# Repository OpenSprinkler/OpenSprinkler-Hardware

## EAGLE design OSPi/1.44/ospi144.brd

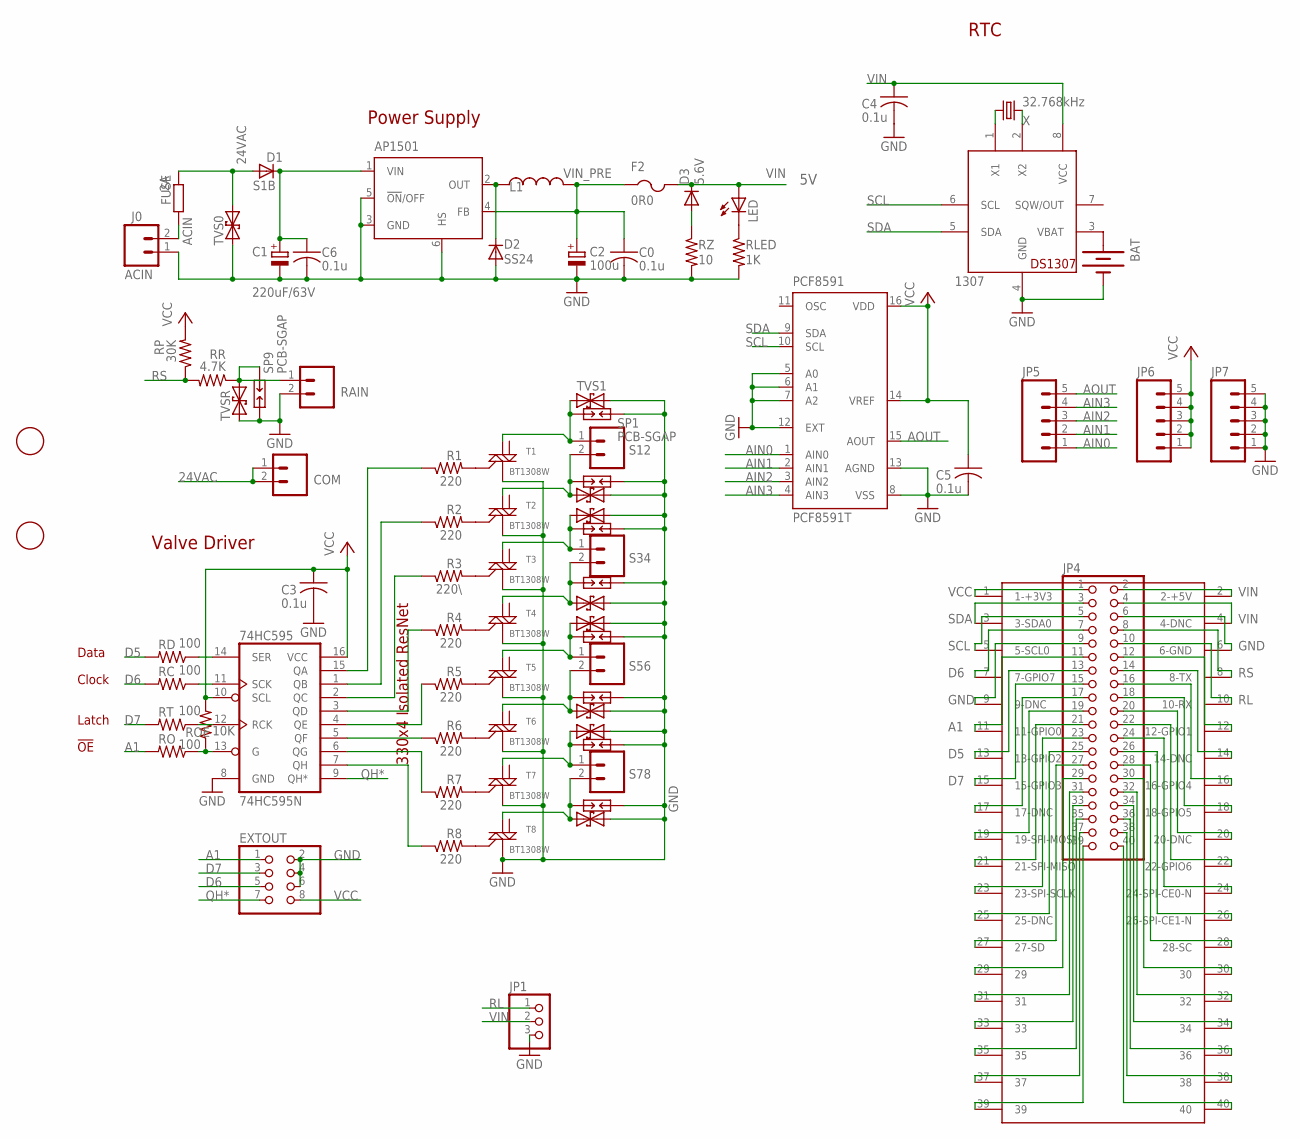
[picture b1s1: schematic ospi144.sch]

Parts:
74HC595: 74HC595N; SO16
1307: DS1307; SO08
AP1501: LM2596S; TO263-5
BAT: BATTERYBATTERY_12MM_SMT; BATTCON_12MM_SMT
C0, C3, C4, C5, C6: 0.1u; C0603K
C1: 220uF/63V; PANASONIC_E
C2: 100u; PANASONIC_E
COM: M025MM-X; SCREWTERMINAL-5MM-2-X
D1: S1B; DO-214AC
D2: SS24; SMB
D3: 5.6V; MINIMELF
EXTOUT: PINHD-2X4/90; 2X04/90
F2: 0R0; 1812
FUSE: 2A; 0207/12
J0: ACIN; SCREWTERMINAL-4MM-2-X
JP1: PINHD-1X3; 1X03
JP4: PINHD-2X20; 2X20
JP5, JP6, JP7: M05PTH; 1X05
L1: 150uH; CDRH125
LED: LEDCHIPLED_0805; CHIPLED_0805
PCF8591: PCF8591T; SO16W
R1, R2, R4, R5, R6, R7, R8: 220; R0603
R3: 220\; R0603
RAIN: M025MM-X; SCREWTERMINAL-5MM-2-X
RC: 100; R0603
RD: 100; R0603
RLED: 1K; R0805
RO: 100; R0603
ROE: 10K; R0603
RP: 30K; R0805
RR: 4.7K; R0805
RT: 100; R0603
RZ: 10; R2010
S12, S34, S56, S78: M025MM-X; SCREWTERMINAL-5MM-2-X
SP1, SP2, SP3, SP4, SP5, SP6, SP7, SP8, SP9: PCB-SGAP
T1, T2, T3, T4, T5, T6, T7, T8: BT1308W; SOT223
TVS0, TVS1, TVS2, TVS3, TVS4, TVS5, TVS6, TVS7, TVS8: TVSSMB; SMB
TVSR: TVSSMB; SMB
U$1, U$3: FIDUCIAL; FIDUCIAL_1MM
U$2: RPIB+
X: 32.768kHz; MM20SS

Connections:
24VAC: COM.1, COM.2, D1.A, FUSE.2, TVS0.C
A1: EXTOUT.1, JP4.11, RO.2, U$2.11 (11-GPIO0)
ACIN: FUSE.1, J0.2
AIN0: JP5.1, PCF8591.1 (AIN0)
AIN1: JP5.2, PCF8591.2 (AIN1)
AIN2: JP5.3, PCF8591.3 (AIN2)
AIN3: JP5.4, PCF8591.4 (AIN3)
AOUT: JP5.5, PCF8591.15 (AOUT)
D5: JP4.13, RD.2, U$2.13 (13-GPIO2)
D6: EXTOUT.5, JP4.7, RC.2, U$2.7 (7-GPIO7)
D7: EXTOUT.3, JP4.15, RT.2, U$2.15 (15-GPIO3)
GND: 74HC595.8 (GND), 1307.4 (GND), AP1501.3 (GND), AP1501.5 (!ON!/OFF), AP1501.6 (HS), BAT.P$1 (-), C0.2, C1.-, C2.-, C3.2, C4.2, C5.2, C6.2, D2.A, EXTOUT.2, EXTOUT.4, EXTOUT.6, J0.1, JP1.3, JP4.6, JP4.9, JP7.1, JP7.2, JP7.3, JP7.4, JP7.5, PCF8591.5 (A0), PCF8591.6 (A1), PCF8591.7 (A2), PCF8591.8 (VSS), PCF8591.12 (EXT), PCF8591.13 (AGND), RAIN.2, RLED.2, RZ.2, SP1.1, SP2.1, SP3.1, SP4.1, SP5.1, SP6.1, SP7.1, SP8.1, SP9.2, T1.1 (M1), T2.1 (M1), T3.1 (M1), T4.1 (M1), T5.1 (M1), T6.1 (M1), T7.1 (M1), T8.1 (M1), TVS0.A, TVS1.C, TVS2.C, TVS3.C, TVS4.C, TVS5.C, TVS6.C, TVS7.C, TVS8.C, TVSR.A, U$2.6 (6-GND), U$2.9 (9-DNC)
unnamed: LED.C, RLED.1
unnamed: AP1501.1 (VIN), C1.+, C6.1, D1.C
unnamed: R1.2, T1.3 (G)
unnamed: 74HC595.5 (QF), R6.1
unnamed: 74HC595.6 (QG), R7.1
unnamed: D3.A, RZ.1
unnamed: 74HC595.7 (QH), R8.1
unnamed: AP1501.2 (OUT), D2.C, L1.1
unnamed: 1307.2 (X2), X.4 (2)
unnamed: 74HC595.4 (QE), R5.1
unnamed: 74HC595.3 (QD), R4.1
unnamed: 74HC595.2 (QC), R3.1
unnamed: 74HC595.1 (QB), R2.1
unnamed: 74HC595.15 (QA), R1.1
unnamed: R2.2, T2.3 (G)
unnamed: S12.1, SP1.2, T1.2 (M2), TVS1.A
unnamed: S12.2, SP2.2, T2.2 (M2), TVS2.A
unnamed: S34.1, SP3.2, T3.2 (M2), TVS3.A
unnamed: R3.2, T3.3 (G)
unnamed: S34.2, SP4.2, T4.2 (M2), TVS4.A
unnamed: R4.2, T4.3 (G)
unnamed: S56.1, SP5.2, T5.2 (M2), TVS5.A
unnamed: S56.2, SP6.2, T6.2 (M2), TVS6.A
unnamed: S78.1, SP7.2, T7.2 (M2), TVS7.A
unnamed: S78.2, SP8.2, T8.2 (M2), TVS8.A
unnamed: R5.2, T5.3 (G)
unnamed: R6.2, T6.3 (G)
unnamed: R7.2, T7.3 (G)
unnamed: R8.2, T8.3 (G)
unnamed: 1307.1 (X1), X.1
unnamed: RAIN.1, RR.1, SP9.1, TVSR.C
unnamed: 74HC595.14 (SER), RD.1
unnamed: 74HC595.11 (SCK), RC.1
unnamed: 74HC595.12 (RCK), RT.1
unnamed: 1307.3 (VBAT), BAT.P$2 (+)
unnamed: JP4.12, U$2.12 (12-GPIO1)
unnamed: JP4.14, U$2.14 (14-DNC)
unnamed: JP4.16, U$2.16 (16-GPIO4)
unnamed: 74HC595.13 (G), RO.1, ROE.1
unnamed: JP4.23, U$2.23 (23-SPI-SCLK)
unnamed: JP4.25, U$2.25 (25-DNC)
unnamed: JP4.27, U$2.27 (27-SD)
unnamed: JP4.29, U$2.29
unnamed: JP4.39, U$2.39
unnamed: JP4.37, U$2.37
unnamed: JP4.17, U$2.17 (17-DNC)
unnamed: JP4.19, U$2.19 (19-SPI-MOSI)
unnamed: JP4.21, U$2.21 (21-SPI-MISO)
unnamed: JP4.35, U$2.35
unnamed: JP4.33, U$2.33
unnamed: JP4.31, U$2.31
unnamed: JP4.34, U$2.34
unnamed: JP4.36, U$2.36
unnamed: JP4.38, U$2.38
unnamed: JP4.40, U$2.40
unnamed: JP4.18, U$2.18 (18-GPIO5)
unnamed: JP4.20, U$2.20 (20-DNC)
unnamed: JP4.22, U$2.22 (22-GPIO6)
unnamed: JP4.24, U$2.24 (24-SPI-CE0-N)
unnamed: JP4.26, U$2.26 (26-SPI-CE1-N)
unnamed: JP4.28, U$2.28 (28-SC)
unnamed: JP4.30, U$2.30
unnamed: JP4.32, U$2.32
QH*: 74HC595.9 (QH*), EXTOUT.7
RL: JP1.1, JP4.10, U$2.10 (10-RX)
RS: JP4.8, RP.1, RR.2, U$2.8 (8-TX)
SCL: 1307.6 (SCL), JP4.5, PCF8591.10 (SCL), U$2.5 (5-SCL0)
SDA: 1307.5 (SDA), JP4.3, PCF8591.9 (SDA), U$2.3 (3-SDA0)
VCC: 74HC595.10 (SCL), 74HC595.16 (VCC), C3.1, C5.1, EXTOUT.8, JP4.1, JP6.1, JP6.2, JP6.3, JP6.4, JP6.5, PCF8591.14 (VREF), PCF8591.16 (VDD), ROE.2, RP.2, U$2.1 (1-+3V3)
VIN: 1307.8 (VCC), C4.1, D3.C, F2.2, JP1.2, JP4.2, JP4.4, LED.A, U$2.2 (2-+5V), U$2.4 (4-DNC)
VIN_PRE: AP1501.4 (FB), C0.1, C2.+, F2.1, L1.2

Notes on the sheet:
Power Supply
Valve Driver
Data
Clock
Latch
330x4 Isolated ResNet
!OE
RTC

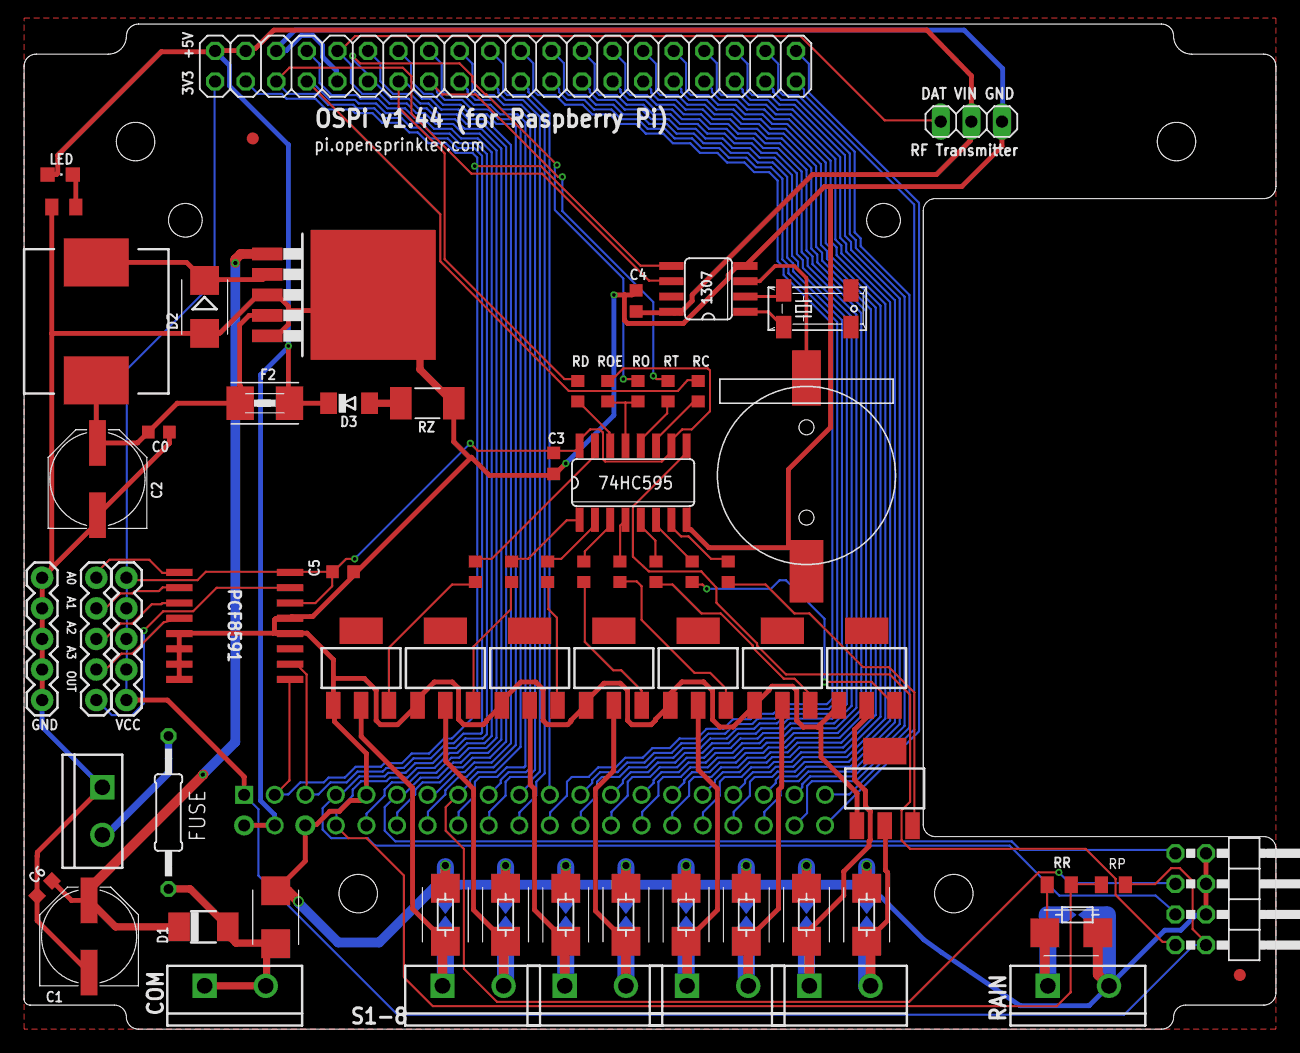
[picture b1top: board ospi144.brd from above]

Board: 2 copper layers, 104.0 x 83.5 mm, 80 parts (1 on the bottom side), 83 nets.
